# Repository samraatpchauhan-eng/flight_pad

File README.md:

# Flight Pad (RP2040 Custom Macro Pad)

Flight Pad is a custom 3x3 mechanical macro pad featuring dual EC11 rotary encoders, built entirely on the high-performance **Raspberry Pi RP2040** microcontroller architecture and powered by **QMK Firmware**. 

It is designed to streamline flight simulator camera controls, and media navigation with zero-latency input processing.

## Features:
* **Custom Layout:** 3x3 Matrix Grid + 1 Integrated Encoder Switch (10 Keys Total).
* **Dual Encoders:** Dual EC11 Encoders for precise, media adjustments (like brightness, or volume).
* **Ergonomic Design:** Engineered for comfortable desktop use.
* **RP2040 Power:** Driven by the RP2040 chip for rapid response times and effortless flashing.

---

## CAD Model & Case Assembly
Everything fits together precisely using a layered enclosure design. The case includes structural mounting points for the PCB, plates, and components to ensure zero deck-flex during heavy use. Please note the keycaps used in these renders are generic .STEP models downloaded from the internet, and any standard MX keycap should work.

### Case Assembly & Fitment Exploded View
*An isometric 3D CAD visualization highlighting how the PCB, switches, encoders, and structural enclosure layers interface together seamlessly.*

---

## PCB Design
The underlying electronics were engineered in KiCad. The board features clean routing paths optimized for the RP2040 pin configurations and a solid matrix layout to handle both the key switches and rotary encoders.

### Schematic Design
*The underlying circuit schematic mapping the switch matrix routing, diode placement, and dual encoder connections to the microcontroller.*

### PCB Layout Architecture
*The routed printed circuit board design detailing trace paths, footprints, and physical alignment.*

---

## Firmware Overview & Default Keymap
This macro pad utilizes **QMK Firmware** for all input processing. The keys are configured in a standard matrix, while the encoders are tracked using hardware interrupts for maximum precision.

### Key Matrix (3x3 Grid)
| Row | Column 1 | Column 2 | Column 3 |
| :--- | :---: | :---: | :---: |
| **Row 0** | `Ctrl+6` | `Ctrl+1` | `Ctrl+7` |
| **Row 1** | `Ctrl+9` | `Ctrl+5` | `Ctrl+8` |
| **Row 2** | `L` | `C` | `R` |

### Rotary Encoder Functionality
* **Encoder 1 (Left/Volume):** * Clockwise: `Volume Up` | Counter-Clockwise: `Volume Down`
  * Integrated Push Switch: `MUTE`
* **Encoder 2 (Right/Brightness):** * Clockwise: `Screen Brightness Down` | Counter-Clockwise: `Screen Brightness Up`

---

## Bill of Materials (BOM)
Here is the complete component breakdown required to build the Flight Pad:

* **9x** Cherry MX Mechanical Switches
* **9x** MX-Compatible Keycaps
* **9x** 1N4148 DO-35 Switching Diodes *(Crucial for matrix isolation and anti-ghosting)*
* **2x** EC11 Rotary Encoders with integrated push-switches
* **1x** Raspberry Pi RP2040 Microcontroller Board
* **1x** Custom Case Enclosure (3D printed/CNC components)
* **4x** M3x16mm screws
* **1x** USB-C wire with data transfer

---

## How to Flash
1. Disconnect the USB cable from the Flight Pad.
2. Press and hold the physical **BOOT** button on the RP2040 controller board.
3. Reconnect the USB cable while holding the button, then release it.
4. A virtual drive named **RPI-RP2** will mount to your operating system.
5. Drag and drop the `flight_pad_default.uf2` binary file directly onto the root of the drive.
6. The device will automatically flash, reboot, and initialize as an operational HID keyboard device.

---

## AI Attribution Note
**Please Note that AI was utilized for some basic debugging of the Keyboard.JSON, and Keymap.C files in VS.Code**

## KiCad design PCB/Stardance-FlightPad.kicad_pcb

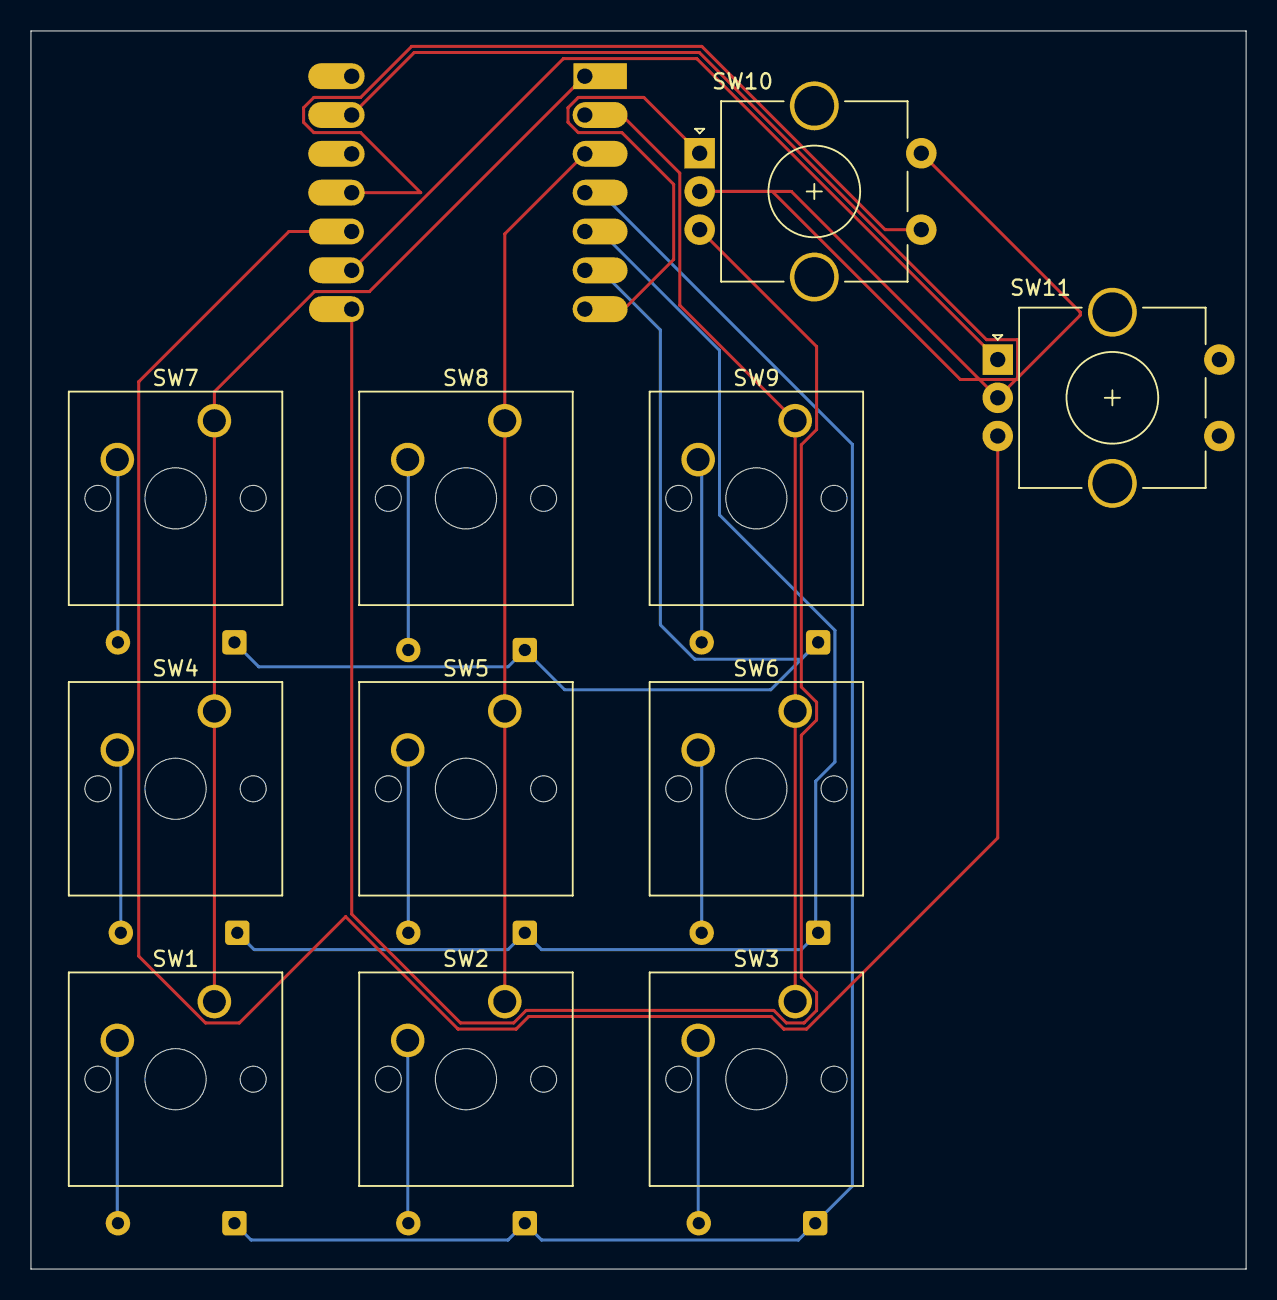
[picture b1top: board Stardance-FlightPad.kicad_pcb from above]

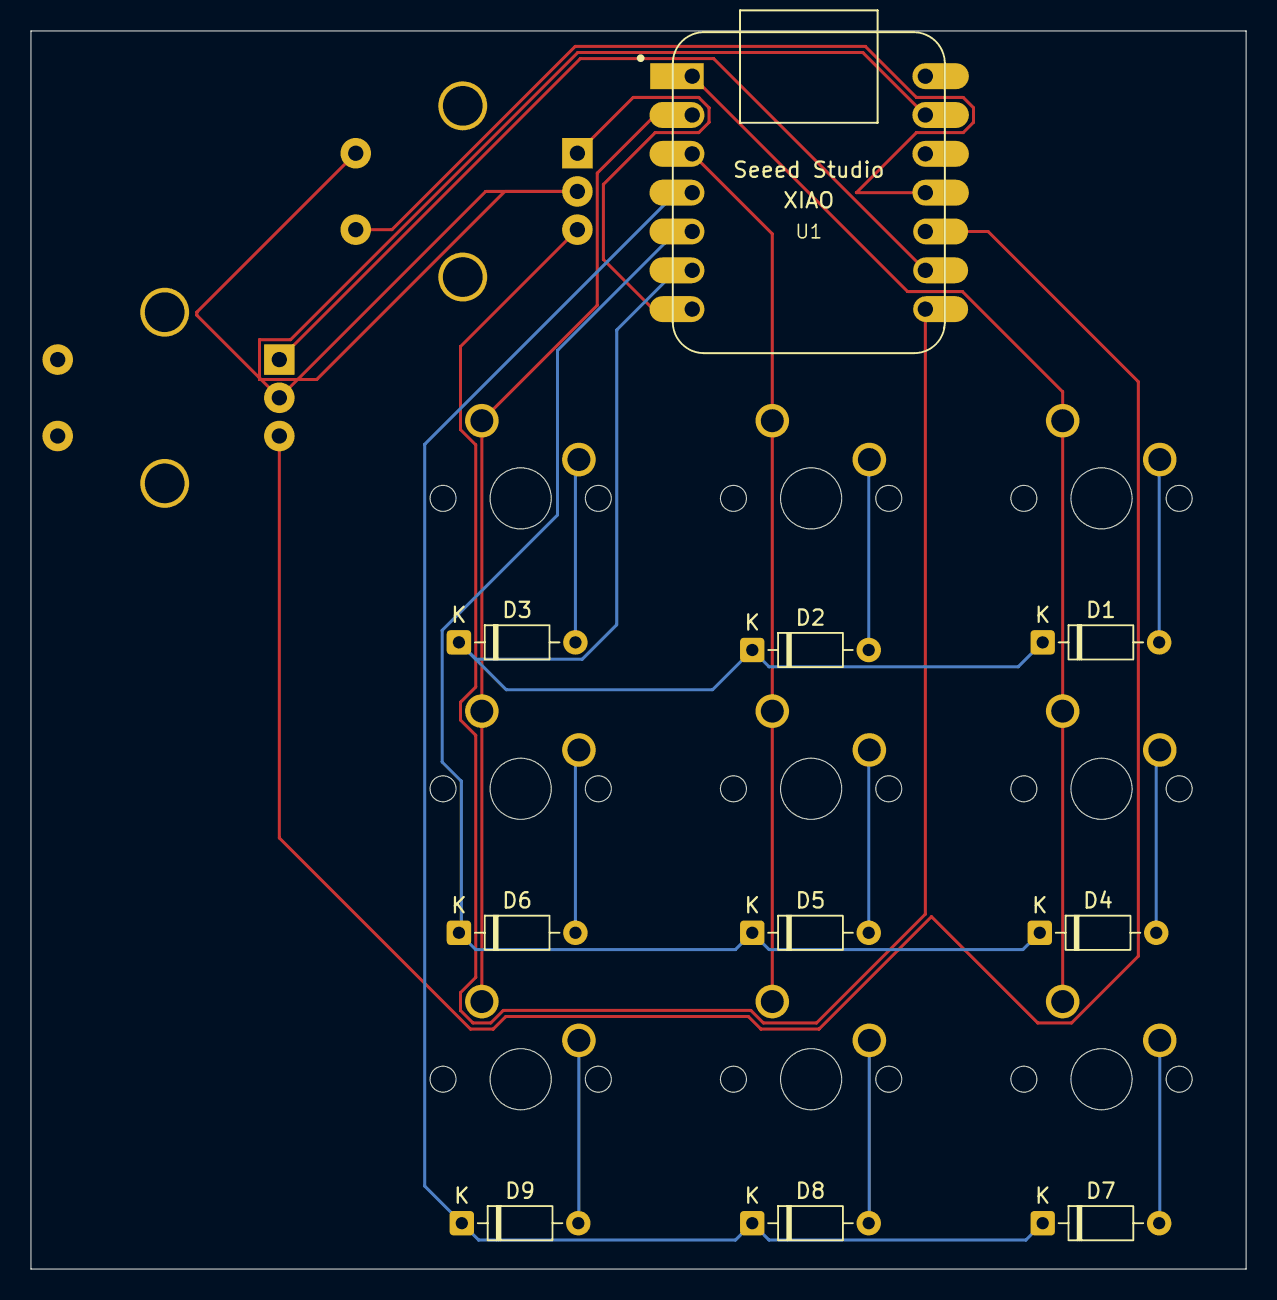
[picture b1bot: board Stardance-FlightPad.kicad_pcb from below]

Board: 2 copper layers, 79.5 x 81.0 mm, 21 parts (10 on the bottom side), 21 nets.

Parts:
D1, D2, D3, D4, D5, D6, D7, D8, D9: 1N4148; D_DO-35_SOD27_P7.62mm_Horizontal
SW1, SW2, SW3, SW4, SW5, SW6, SW7, SW8, SW9: SW_Push; SW_Cherry_MX_1.00u_PCB
SW10, SW11: RotaryEncoder_Switch; RotaryEncoder_Alps_EC11E-Switch_Vertical_H20mm_CircularMoun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
U1: MOUDLE-SEEEDUINO-XIAO; XIAO-Generic-Hybrid-14P-2.54-21X17.8MM

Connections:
/COL0: SW1.1, SW4.1, SW7.1, U1.1 (PA02_A0_D0)
/COL1: SW2.1, SW5.1, SW8.1, U1.3 (PA10_A2_D2)
/COL2: SW3.1, SW6.1, SW9.1, U1.2 (PA4_A1_D1)
/ENC1_A: SW10.A, U1.7 (PB08_A6_D6_TX)
/ENC1_B: SW10.B, U1.8 (PB09_A7_D7_RX)
/ENC1_SW: SW10.S1, U1.11 (PA6_A10_D10_MOSI)
/ENC2_A: SW11.A, U1.9 (PA7_A8_D8_SCK)
/ENC2_B: SW11.B, U1.10 (PA5_A9_D9_MISO)
/ROW0: D1.1 (K), D2.1 (K), D3.1 (K), U1.6 (PA9_A5_D5_SCL)
/ROW1: D4.1 (K), D5.1 (K), D6.1 (K), U1.5 (PA8_A4_D4_SDA)
/ROW2: D7.1 (K), D8.1 (K), D9.1 (K), U1.4 (PA11_A3_D3)
GND: SW10.C, SW10.S2, SW11.C, U1.13 (GND)
unnamed: D1.2 (A), SW7.2
unnamed: D2.2 (A), SW8.2
unnamed: D3.2 (A), SW9.2
unnamed: D4.2 (A), SW4.2
unnamed: D5.2 (A), SW5.2
unnamed: D6.2 (A), SW6.2
unnamed: D7.2 (A), SW1.2
unnamed: D8.2 (A), SW2.2
unnamed: D9.2 (A), SW3.2

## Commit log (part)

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2026-06-16 Revise README with comprehensive project details
    Expanded README to include detailed features, assembly instructions, PCB design, firmware overview, and BOM for the Flight Pad project.
2026-06-16 Add PCB Layout image to README
2026-06-19 Refactor README.md for improved clarity and formatting
    Updated section headers and formatting in README.md.
2026-06-27 Update components list in README
    Added USB-C wire with data transfer to the components list.
